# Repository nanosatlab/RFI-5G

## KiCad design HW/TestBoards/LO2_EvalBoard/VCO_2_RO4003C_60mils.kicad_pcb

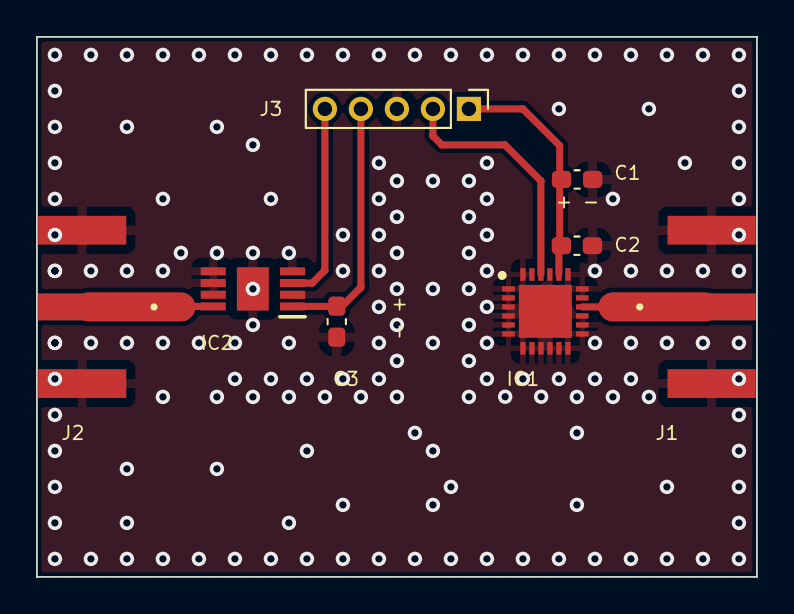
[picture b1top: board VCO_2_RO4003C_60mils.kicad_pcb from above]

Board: 2 copper layers, 40.0 x 30.0 mm, 8 parts (0 on the bottom side), 7 nets.

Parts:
C1: 4.7 uF; C_0603_1608Metric_Pad1.08x0.95mm_HandSolder
C2: 10 nF; C_0603_1608Metric_Pad1.08x0.95mm_HandSolder
C3: 10 uF; C_0603_1608Metric_Pad1.08x0.95mm_HandSolder
IC1: HMC506LP4E; QFN50P400X400X100-25N
IC2: HMC358MS8GE; SOP65P488X110-9N
J1, J2: SMA; LINX_CONSMA020.062-G
J3: Conn_01x05; PinHeader_1x05_P2.00mm_Vertical

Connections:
/RF_out_1: IC1.16 (RFOUT), J1.1 (RF)
/RF_out_2: IC2.8 (RFOUT), J2.1 (RF)
/Vcc_1: C1.1, C2.1, IC1.20 (VCC), J3.1
/Vcc_2: C3.1, IC2.1 (VCC), J3.4
/Vtune_1: IC1.22 (VTUNE), J3.2
/Vtune_2: IC2.3 (VTUNE), J3.5
GND: C1.2, C2.2, C3.2, IC1.1 (N/C_1), IC1.2 (N/C_2), IC1.3 (N/C_3), IC1.4 (N/C_4), IC1.5 (N/C_5), IC1.6 (N/C_6), IC1.7 (N/C_7), IC1.8 (N/C_8), IC1.9 (N/C_9), IC1.10 (N/C_10), IC1.11 (N/C_11), IC1.12 (N/C_12), IC1.13 (N/C_13), IC1.14 (N/C_14), IC1.15 (GND), IC1.17 (N/C_15), IC1.18 (N/C_16), IC1.19 (N/C_17), IC1.21 (N/C_18), IC1.23 (N/C_19), IC1.24 (N/C_20), IC1.25 (EP), IC2.2 (N/C_1), IC2.4 (GND_1), IC2.5 (GND_2), IC2.6 (N/C_2), IC2.7 (N/C_3), IC2.9 (EP), J1.S1, J1.S2, J1.S3, J1.S4, J2.S1, J2.S2, J2.S3, J2.S4, J3.3

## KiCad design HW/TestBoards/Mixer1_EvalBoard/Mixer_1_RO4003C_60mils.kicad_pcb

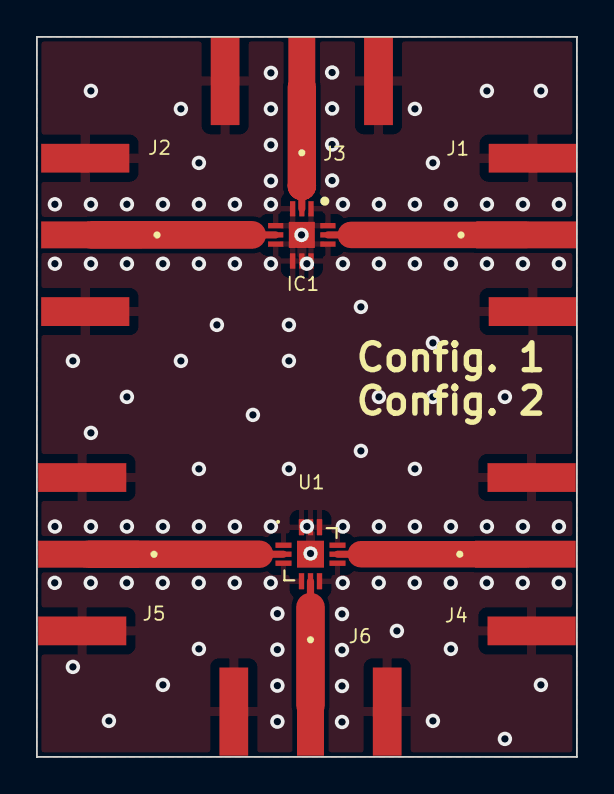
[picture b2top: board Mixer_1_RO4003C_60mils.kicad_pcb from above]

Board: 2 copper layers, 30.0 x 40.0 mm, 8 parts (0 on the bottom side), 7 nets.

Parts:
IC1: MDB-44H+; QFN51P300X300X89-13N
J1, J2, J3, J4, J5, J6: SMA; LINX_CONSMA020.062-G
U1: HMC260ALC3B

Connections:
/IF 4.1: IC1.2 (IF-OUT), J3.1 (RF)
/IF 4.2: J6.1 (RF), U1.5 (IF)
/LO 4.1: IC1.5 (LO-IN), J2.1 (RF)
/LO 4.2: J5.1 (RF), U1.2 (LO)
/RF 4.1: IC1.11 (RF-IN), J1.1 (RF)
/RF 4.2: J4.1 (RF), U1.8 (RF)
GND1: IC1.1 (GND_1), IC1.3 (GND_2), IC1.4 (GND_3), IC1.6 (GND_4), IC1.7 (N/C_1), IC1.8 (N/C_2), IC1.9 (N/C_3), IC1.10 (GND_5), IC1.12 (GND_6), IC1.13 (EP), J1.S1, J1.S2, J1.S3, J1.S4, J2.S1, J2.S2, J2.S3, J2.S4, J3.S1, J3.S2, J3.S3, J3.S4, J4.S1, J4.S2, J4.S3, J4.S4, J5.S1, J5.S2, J5.S3, J5.S4, J6.S1, J6.S2, J6.S3, J6.S4, U1.1 (GND), U1.3 (GND), U1.4 (GND), U1.6 (GND), U1.7 (GND), U1.9 (GND), U1.10 (NIC), U1.11 (NIC), U1.12 (NIC), U1.13 (GND_(EP))
